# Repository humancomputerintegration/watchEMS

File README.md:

# Can a Smartwatch Move Your Fingers? 

This repository contains the source code used in the research publication "Can a Smartwatch Move Your Fingers?" from the [Human-Computer Integration Lab](https://lab.plopes.org/) at the University of Chicago.

## Citing

When using or building upon this device in an academic publication, please consider citing as follows:

ACM Reference Format: Akifumi Takahashi, Yudai Tanaka, Archit Tamhane, Alan Shen, Shan-Yuan Teng, and Pedro Lopes. 2024. Can a Smartwatch Move Your Fingers? Compact and Practical Electrical Muscle Stimulation in a Smartwatch. In The 37th Annual ACM Symposium on User Interface Software and Technology (UIST ’24), October 13–16, 2024, Pittsburgh, PA, USA. ACM, New York, NY, USA, 15 pages. https://doi.org/10.1145/3654777.3676373

## Contact

For any questions about this repository, please contact yudaitanaka@uchicago.edu

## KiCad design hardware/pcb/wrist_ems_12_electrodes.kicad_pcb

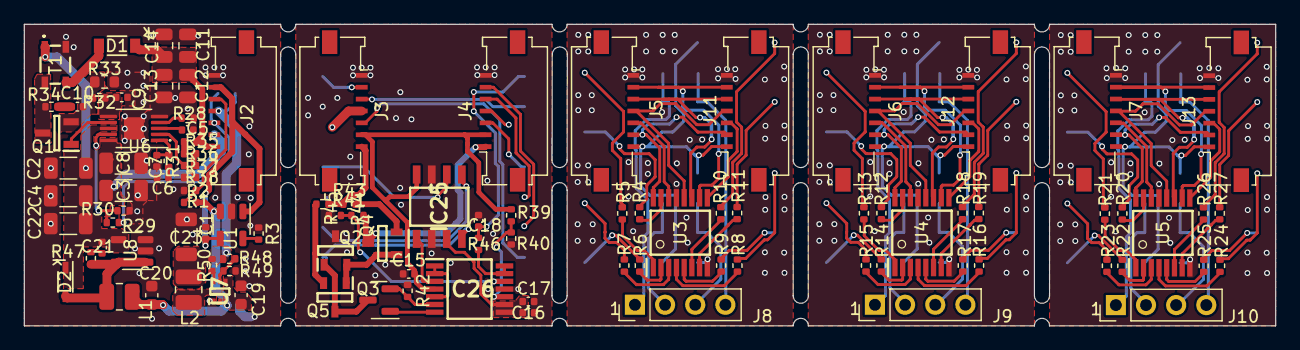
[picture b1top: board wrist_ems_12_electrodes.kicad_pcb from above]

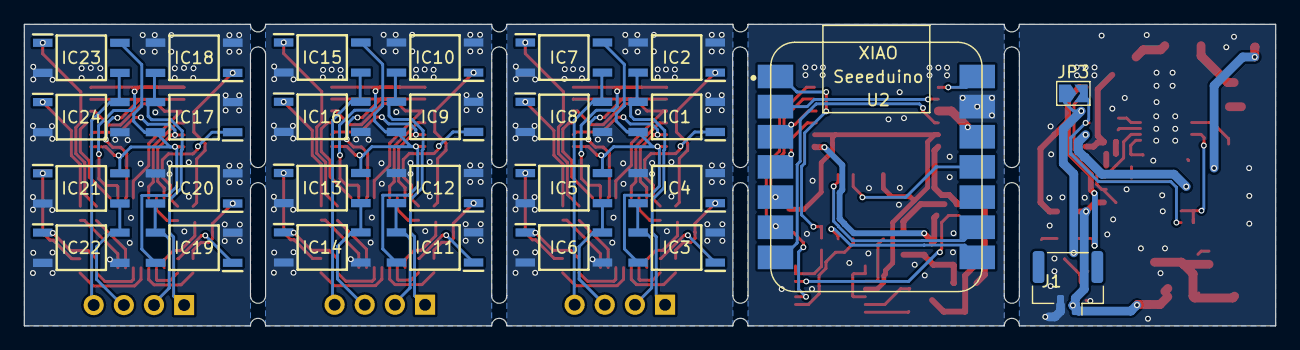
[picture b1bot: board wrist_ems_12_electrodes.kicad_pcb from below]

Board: 2 copper layers, 105.4 x 25.4 mm, 131 parts (27 on the bottom side), 140 nets.

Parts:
C1, C18: 1nF; C_0402_1005Metric
C2, C3, C4, C8, C22, C23: 47uF; C_1206_3216Metric
C5: 0.1uF; C_0402_1005Metric
C6: 22nF; C_0402_1005Metric
C7: 100pF; C_0402_1005Metric
C9: 10nF; C_0402_1005Metric
C10: 220pF; C_0402_1005Metric
C11, C12, C13, C14: 100nF; C_0805_2012Metric
C15, C16: 100nF; C_0402_1005Metric
C17: 10uF; C_0402_1005Metric
C19, C20: 4.7uF; C_0603_1608Metric
C21: 120pF; C_0402_1005Metric
D1: RF081MM2STR
D2: NSVR1020MW2T1G; SOD2512X110N
IC1, IC2, IC3, IC4, IC5, IC6, IC7, IC8, IC9, IC10, IC11, IC12, IC13, IC14, IC15, IC16, IC17, IC18, IC19, IC20, IC21, IC22, IC23, IC24: TLP188_TPL,E; SOP254P700X220-4N
IC25: DAC8830ID; SOIC127P600X175-8N
IC26: OPA4205APWT; SOP65P640X120-14N
J1: Conn_01x02_Pin; JST_GH_SM02B-GHS-TB_1x02-1MP_P1.25mm_Horizontal
J2, J3, J4, J5, J6, J7, J11, J12, J13: Conn_01x07_Pin; Molex_200528-0070_1x07-1MP_P1.00mm_Horizontal
J8, J9, J10: Conn_01x04_Pin; PinHeader_1x04_P2.54mm_Vertical
JP3: Jumper_2_Open; SolderJumper-2_P1.3mm_Open_TrianglePad1.0x1.5mm
L1: 4.7uH; L_1008_2520Metric
L2: 1uH; L_1008_2520Metric
Q1: RSR030N06TL; SOT95P280X100-3N
Q2, Q4, Q5: MMBTA92LT1G; SOT96P237X111-3N
Q3: DMN30H4D0L; SOT-23
R1, R2, R29, R49: 100k; R_0402_1005Metric
R3: 10k; R_0402_1005Metric
R4, R5, R6, R7, R8, R9, R10, R11, R12, R13, R14, R15, R16, R17, R18, R19, R20, R21, R22, R23, R24, R25, R26, R27: 330; R_0402_1005Metric
R28: 130k(100kHz); R_0402_1005Metric
R30: 240k; R_0402_1005Metric
R31: 6.8k; R_0402_1005Metric
R32, R34, R47: 22; R_0402_1005Metric
R33: 0.02; R_0603_1608Metric
R35, R36, R37, R50: 499k; R_0402_1005Metric
R38: 16k; R_0402_1005Metric
R39: 300k; R_0402_1005Metric
R40: 200k; R_0402_1005Metric
R41: 1k; R_0402_1005Metric
R42: 1k3; R_0402_1005Metric
R43, R46: 100; R_0402_1005Metric
R44: 1M; R_0402_1005Metric
R45: 30k; R_0402_1005Metric
R48: 453k; R_0402_1005Metric
T1: ATB322515-0110-T000; ATB3225150110T000
U1: MCP73812T-420I-OT; SOT-23-5
U2: SeeeduinoXIAO_onlyPinHeader; XIAO-nRF52840-Sense-14P-2.54-21X17.8MM)_onlyPins
U3, U4, U5: 74AHCT595; SOP65P640X110-16N
U6: LT3757AEMSE; MSOP-10-1EP_3x3mm_P0.5mm_EP1.68x1.88mm
U7: XPS62A01DRLR; SOTFL50P160X60-6N
U8: TPS613222ADBV; SOT-23-5

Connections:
3V3: J3.4, U2.12 (3V3)
5V: C15.2, IC25.8 (VDD), IC26.4 (V+), J3.6, J4.2, R39.2
150V: J3.7, R41.1, R43.1
/SR_PhotoSW_4ch_out1/CH1: IC9.3 (E), IC10.4 (C), J9.1
/SR_PhotoSW_4ch_out1/CH2: IC11.3 (E), IC12.4 (C), J9.2
/SR_PhotoSW_4ch_out1/CH3: IC13.3 (E), IC14.4 (C), J9.3
/SR_PhotoSW_4ch_out1/CH4: IC15.3 (E), IC16.4 (C), J9.4
/SR_PhotoSW_4ch_out1/SR1Q1: R12.2, U4.15 (QA)
/SR_PhotoSW_4ch_out1/SR1Q2: R13.2, U4.1 (QB)
/SR_PhotoSW_4ch_out1/SR1Q3: R14.2, U4.2 (QC)
/SR_PhotoSW_4ch_out1/SR1Q4: R15.2, U4.3 (QD)
/SR_PhotoSW_4ch_out1/SR1Q5: R16.2, U4.4 (QE)
/SR_PhotoSW_4ch_out1/SR1Q6: R17.2, U4.5 (QF)
/SR_PhotoSW_4ch_out1/SR1Q7: R18.2, U4.6 (QG)
/SR_PhotoSW_4ch_out1/SR1Q8: R19.2, U4.7 (QH)
/SR_PhotoSW_4ch_out2/CH1: IC17.3 (E), IC18.4 (C), J10.1
/SR_PhotoSW_4ch_out2/CH2: IC19.3 (E), IC20.4 (C), J10.2
/SR_PhotoSW_4ch_out2/CH3: IC21.3 (E), IC22.4 (C), J10.3
/SR_PhotoSW_4ch_out2/CH4: IC23.3 (E), IC24.4 (C), J10.4
/SR_PhotoSW_4ch_out2/SR1Q1: R20.2, U5.15 (QA)
/SR_PhotoSW_4ch_out2/SR1Q2: R21.2, U5.1 (QB)
/SR_PhotoSW_4ch_out2/SR1Q3: R22.2, U5.2 (QC)
/SR_PhotoSW_4ch_out2/SR1Q4: R23.2, U5.3 (QD)
/SR_PhotoSW_4ch_out2/SR1Q5: R24.2, U5.4 (QE)
/SR_PhotoSW_4ch_out2/SR1Q6: R25.2, U5.5 (QF)
/SR_PhotoSW_4ch_out2/SR1Q7: R26.2, U5.6 (QG)
/SR_PhotoSW_4ch_out2/SR1Q8: R27.2, U5.7 (QH)
/SR_PhotoSW_4ch_out/CH1: IC1.3 (E), IC2.4 (C), J8.1
/SR_PhotoSW_4ch_out/CH2: IC3.3 (E), IC4.4 (C), J8.2
/SR_PhotoSW_4ch_out/CH3: IC5.3 (E), IC6.4 (C), J8.3
/SR_PhotoSW_4ch_out/CH4: IC7.3 (E), IC8.4 (C), J8.4
/SR_PhotoSW_4ch_out/SR1Q1: R4.2, U3.15 (QA)
/SR_PhotoSW_4ch_out/SR1Q2: R5.2, U3.1 (QB)
/SR_PhotoSW_4ch_out/SR1Q3: R6.2, U3.2 (QC)
/SR_PhotoSW_4ch_out/SR1Q4: R7.2, U3.3 (QD)
/SR_PhotoSW_4ch_out/SR1Q5: R8.2, U3.4 (QE)
/SR_PhotoSW_4ch_out/SR1Q6: R9.2, U3.5 (QF)
/SR_PhotoSW_4ch_out/SR1Q7: R10.2, U3.6 (QG)
/SR_PhotoSW_4ch_out/SR1Q8: R11.2, U3.7 (QH)
/dcdc_5v_to_100V/Rsense: C10.2, Q1.2, R32.1, R33.2
/dcdc_5v_to_100V/Sense: C9.1, R32.2, U6.6 (SENSE)
/dcdc_5v_to_100V/dcdc_150V_SW: Q1.3, R34.1, T1.4
/dcdc_bat_to_3v3_5v/PG_3V3: R50.1, U7.6 (PG)
/dcdc_bat_to_3v3_5v/dcdc_3V3_SW: L2.1, U7.2 (SW)
/vol_to_curr/2V: C16.2, C17.2, IC25.3 (VREF), IC26.8, IC26.9 (-)
CLR: J4.6, U2.6 (PA9_A5_D5_SCL)
CUR_OUT: J4.1, Q4.3 (C), R44.1
CUR_vol: C18.2, R46.2, U2.1 (PA02_A0_D0)
DAC_MOSI: IC25.6 (SDI), U2.11 (PA6_A10_D10_MOSI)
DAC_SCK: IC25.5 (SCLK), U2.9 (PA7_A8_D8_SCK)
DAC_nCS: IC25.4 (~CS), U2.8 (PB09_A7_D7_RX)
DI: J4.3, U2.4 (PA11_A3_D3)
EN_150V: J3.5, U2.7 (PB08_A6_D6_TX)
GND: C15.1, C16.1, C17.1, C18.1, IC25.2 (AGND), IC25.7 (DGND), IC26.11 (V-), J3.1, J4.7, Q2.3 (C), R40.2, R42.2, R45.2, U2.13 (GND)
GNDA: C1.1, C2.2, C3.2, C4.2, C5.2, C6.2, C7.2, C8.2, C9.2, C11.2, C12.2, C13.2, C14.2, C19.2, C20.2, C22.2, C23.2, J1.2, J2.7, R2.2, R3.2, R28.1, R30.2, R33.1, R38.1, R49.2, T1.2, U1.2 (V_{SS}), U6.5 (SYNC), U6.11 (GND), U7.1 (GND), U8.2 (GND), U8.3 (NC)
unnamed: C6.1, R31.2
unnamed: C10.1, R34.2
unnamed: C21.1, R47.1
unnamed: D1.2 (A), T1.3
unnamed: D2.2 (A), L1.2, R47.2, U8.1 (SW), U8.5 (NC)
unnamed: IC1.1 (A), R4.1
unnamed: IC2.1 (A), R5.1
unnamed: IC3.1 (A), R6.1
unnamed: IC4.1 (A), R7.1
unnamed: IC5.1 (A), R8.1
unnamed: IC6.1 (A), R9.1
unnamed: IC7.1 (A), R10.1
unnamed: IC8.1 (A), R11.1
unnamed: IC9.1 (A), R12.1
unnamed: IC10.1 (A), R13.1
unnamed: IC11.1 (A), R14.1
unnamed: IC12.1 (A), R15.1
unnamed: IC13.1 (A), R16.1
unnamed: IC14.1 (A), R17.1
unnamed: IC15.1 (A), R18.1
unnamed: IC16.1 (A), R19.1
unnamed: IC17.1 (A), R20.1
unnamed: IC18.1 (A), R21.1
unnamed: IC19.1 (A), R22.1
unnamed: IC20.1 (A), R23.1
unnamed: IC21.1 (A), R24.1
unnamed: IC22.1 (A), R25.1
unnamed: IC23.1 (A), R26.1
unnamed: IC24.1 (A), R27.1
unnamed: IC25.1 (VOUT), IC26.3 (+)
unnamed: IC26.1, IC26.2 (-), IC26.5 (+)
unnamed: IC26.6 (-), Q3.2 (S), R42.1
unnamed: IC26.10 (+), R39.1, R40.1
unnamed: IC26.12 (+), R44.2, R45.1
unnamed: IC26.13 (-), IC26.14, R46.1
unnamed: Q2.1 (B), Q3.3 (D), Q5.3 (C)
unnamed: Q2.2 (E), Q4.1 (B), Q5.1 (B)
unnamed: IC26.7, Q3.1 (G)
unnamed: Q4.2 (E), R43.2
unnamed: Q5.2 (E), R41.2
unnamed: R35.1, R36.2
unnamed: R36.1, R37.2
unnamed: R3.1, U1.5 (PROG)
unnamed: R37.1, R38.2, U6.2 (FBX)
unnamed: Q1.1, U6.7 (GATE)
unnamed: R28.2, U6.4 (RT)
unnamed: C5.1, U6.3 (SS)
unnamed: C7.1, R31.1, U6.1 (VC)
unnamed: R29.1, R30.1, U6.9 (~SHDN/UVLO)
unnamed: R48.2, R49.1, U7.5 (FB)
RCK: J4.4, U2.3 (PA10_A2_D2)
SCK: J4.5, U2.5 (PA8_A4_D4_SDA)
Vbat: C19.1, C20.1, J1.1, L1.1, R1.1, U1.3 (V_{BAT}), U7.3 (VIN), U7.4 (EN)
bat_vol: J3.3, U2.2 (PA4_A1_D1)
dcdc_3V3: C23.1, J2.4, JP3.1 (A), L2.2, R48.1, R50.2
dcdc_5V: C2.1, C3.1, C4.1, C8.1, C21.2, C22.1, D2.1 (K), J2.2, T1.1, U6.8 (INTVCC), U6.10 (VIN), U8.4 (VOUT)
dcdc_150V: C11.1, C12.1, C13.1, C14.1, D1.1 (K), J2.1, R35.2
dcdc_EN_150V: J2.3, JP3.2 (B), R29.2
dcdc_bat_vol: J2.5, R1.2, R2.1
dcdc_usb_5V: C1.2, J2.6, U1.1 (CE), U1.4 (V_{DD})
sw1_5v: J5.6, J11.2, U3.16 (VCC)
sw1_clr: J5.2, J11.6, U3.10 (~SRCLR)
sw1_di: J5.5, U3.14 (SER)
sw1_do: J11.3, U3.9 (QH')
sw1_gnd: IC1.2 (K), IC2.2 (K), IC2.3 (E), IC3.2 (K), IC4.2 (K), IC4.3 (E), IC5.2 (K), IC6.2 (K), IC6.3 (E), IC7.2 (K), IC8.2 (K), IC8.3 (E), J5.1, J11.7, U3.8 (GND), U3.13 (~OE)
sw1_rck: J5.4, J11.4, U3.12 (RCLK)
sw1_sck: J5.3, J11.5, U3.11 (SRCLK)
sw1_vcc: IC1.4 (C), IC3.4 (C), IC5.4 (C), IC7.4 (C), J5.7, J11.1
sw2_5v: J6.6, J12.2, U4.16 (VCC)
sw2_clr: J6.2, J12.6, U4.10 (~SRCLR)
sw2_di: J6.5, U4.14 (SER)
sw2_gnd: IC9.2 (K), IC10.2 (K), IC10.3 (E), IC11.2 (K), IC12.2 (K), IC12.3 (E), IC13.2 (K), IC14.2 (K), IC14.3 (E), IC15.2 (K), IC16.2 (K), IC16.3 (E), J6.1, J12.7, U4.8 (GND), U4.13 (~OE)
sw2_rck: J6.4, J12.4, U4.12 (RCLK)
sw2_sck: J6.3, J12.5, U4.11 (SRCLK)
sw2_vcc: IC9.4 (C), IC11.4 (C), IC13.4 (C), IC15.4 (C), J6.7, J12.1
sw3_5v: J7.6, J13.2, U5.16 (VCC)
sw3_clr: J7.2, J13.6, U5.10 (~SRCLR)
sw3_di: J7.5, U5.14 (SER)
sw3_do: J13.3, U5.9 (QH')
sw3_gnd: IC17.2 (K), IC18.2 (K), IC18.3 (E), IC19.2 (K), IC20.2 (K), IC20.3 (E), IC21.2 (K), IC22.2 (K), IC22.3 (E), IC23.2 (K), IC24.2 (K), IC24.3 (E), J7.1, J13.7, U5.8 (GND), U5.13 (~OE)
sw3_rck: J7.4, J13.4, U5.12 (RCLK)
sw3_sck: J7.3, J13.5, U5.11 (SRCLK)
sw3_vcc: IC17.4 (C), IC19.4 (C), IC21.4 (C), IC23.4 (C), J7.7, J13.1
sw_do: J12.3, U4.9 (QH')
usb_5V: J3.2, U2.14 (5V)

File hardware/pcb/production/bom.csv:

Designator,Footprint,Quantity,Value,LCSC Part #,,,,
"C1, C18",0402,2,1nF,C1523,,,,
C10,0402,1,220pF,C1530,,,,
"C11, C12, C13, C14",0805,4,100nF,C5331016,,,,
"C15, C16",0402,2,100nF,C9900048290,,,,
C17,0402,1,10uF,C408132,,,,
"C19, C20",0603,2,4.7uF,C19666,,,,
"C2, C22, C23, C3, C4, C8",1206,6,47uF,C76659,,,,
C21,0402,1,120pF,C695379,,,,
C5,0402,1,0.1uF,C1525,,,,
C6,0402,1,22nF,C1532,,,,
C7,0402,1,100pF,C1546,,,,
C9,0402,1,10nF,C15195,,,,
D1,RF081MM2STR,1,RF081MM2STR,C509966,,,,
D2,SOD2512X110N,1,NSVR1020MW2T1G,C893984,,,,
"IC1, IC10, IC11, IC12, IC13, IC14, IC15, IC16, IC17, IC18, IC19, IC2, IC20, IC21, IC22, IC23, IC24, IC3, IC4, IC5, IC6, IC7, IC8, IC9",SOP254P700X220-4N,24,"TLP188_TPL,E",C4153840,,,,
IC25,SOIC127P600X175-8N,1,DAC8830ID,C42816,,,,
IC26,SOP65P640X120-14N,1,OPA4205APWT,C20345595,,,,
J1,JST_GH_SM02B-GHS-TB_1x02-1MP_P1.25mm_Horizontal,1,Conn_01x02_Pin,C189893,,,,
"J10, J8, J9",PinHeader_1x04_P2.54mm_Vertical,3,Conn_01x04_Pin,,,,,
"J11, J12, J13, J2, J3, J4, J5, J6, J7",Molex_200528-0070_1x07-1MP_P1.00mm_Horizontal,9,Conn_01x07_Pin,C6369987,,,,
JP3,SolderJumper-2_P1.3mm_Open_TrianglePad1.0x1.5mm,1,Jumper_2_Open,,,,,
L1,1008,1,4.7uH,C668313,,,,
L2,1008,1,1uH,C435392,,,,
Q1,SOT95P280X100-3N,1,RSR030N06TL,C126317,,,,
"Q2, Q4, Q5",SOT96P237X111-3N,3,MMBTA92LT1G,C82049,,,,
Q3,SOT-23,1,DMN30H4D0L,C461015,,,,
"R1, R2, R29, R49",0402,4,100k,C25741,,,,
"R10, R11, R12, R13, R14, R15, R16, R17, R18, R19, R20, R21, R22, R23, R24, R25, R26, R27, R4, R5, R6, R7, R8, R9",0402,24,330,C25104,,,,
R28,0402,1,130k(100kHz),C409851,,,,
R3,0402,1,2k,C4109,,,,
R30,0402,1,240k,C413113,,,,
R31,0402,1,6.8k,C409870,,,,
"R32, R34, R47",0402,3,22,C413049,,,,
R33,0603,1,0.02,C2088537,,,,
"R35, R36, R37",0402,3,499k, C2986233,,,,
R38,0402,1,16k,C409889,,,,
R39,0402,1,300k,C131560,,,,
R40,0402,1,200k,C131534,,,,
R41,0402,1,1k,C445596,,,,
R42,0402,1,1k3,C336808,,,,
R43,0402,1,100, C491157,,,,
R44,0402,1,1M,C413126,,,,
R45,0402,1,30k,C413010,,,,
R46,0402,1,100,C25077,,,,
R48,0402,1,453k,C27009,,,,
R50,0402,1,499k,C25793,,,,
T1,ATB3225150110T000,1,ATB322515-0110-T000,C415291,,,,
U1,SOT-23-5,1,MCP73812T-420I-OT,C144308,,,,
U2,XIAO-nRF52840-Sense-14P-2.54-21X17.8MM)_onlyPins,1,SeeeduinoXIAO_onlyPinHeader,,,,,
"U3, U4, U5",SOP65P640X110-16N,3,74AHCT595,C554707,,,,
U6,MSOP-10-1EP_3x3mm_P0.5mm_EP1.68x1.88mm,1,LT3757AEMSE,C671465,,,,
U7,SOTFL50P160X60-6N,1,XPS62A01DRLR,C5157937,,,,
U8,SOT-23-5,1,TPS613222ADBV,C2071163,,,,
,,,,,,,,
ffc calble,7pin pitch1mm 30mm,,0152670745,,,Molex,0152670745,https://www.digikey.com/en/products/detail/molex/0152670745/4427495
ffc calble,7pin pitch1mm 50mm,,0152670747,,,Molex,0152670747,https://www.digikey.com/en/products/detail/molex/0152670747/4427497
ffc calble,7pin pitch1mm 70mm,,0151670749,,,Molex,0151670749,https://www.digikey.com/en/products/detail/molex/0151670749/4426466
ffc calble,7pin pitch1mm 76mm,,10-07-A-0076-C-4-08-4-T,,,GCT,10-07-A-0076-C-4-08-4-T,https://www.digikey.jp/ja/products/detail/gct/10-07-A-0076-C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
ffc calble,7pin pitch1mm 50mm,,10-07-A-0050-C-4-08-4-T,,,GCT,10-07-A-0050-C-4-08-4-T,https://www.digikey.jp/ja/products/detail/gct/10-07-A-0050-C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
ffc calble,7pin pitch1mm 152mm,,10-07-A-0152-C-4-08-4-T,,,GCT,10-07-A-0152-C-4-08-4-T,https://www.digikey.jp/ja/products/detail/gct/10-07-A-0152-C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
ffc calble,7pin pitch1mm 100mm,,10-07-A-0101-C-4-08-4-T,,,GCT,10-07-A-0101-C-4-08-4-T,https://www.digikey.jp/ja/products/detail/gct/10-07-A-0101-C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
,,,,,,,,
battery,,,,,,,,https://www.amazon.com/gp/product/B09WK78594/ref=ppx_yo_dt_b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
,,,DTP401525(EZ3),,,,,https://www.marutsu.co.jp/pc/i/2228265/
J1,,,SM02B-SRSS-TB,,,,SM02B-SRSS-TB,https://www.digikey.jp/ja/products/detail/jst-sales-america-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
J1 housing,,,SHR-02V-S-B,,,,SHR-02V-S-B,https://www.digikey.jp/ja/products/detail/jst-sales-america-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

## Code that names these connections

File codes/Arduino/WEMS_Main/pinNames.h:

/** Pin name aliases
 *  
 *      somwhow "int PIN_VOL_CUR = P0_2;" or so didn't work well. so here I defined them using #define macro. 
 *      if you find a better way, please modify it.
 */
#ifndef PIN_NAMES_H
#define PIN_NAMES_H

#define  PIN_VOL_CUR    P0_2    //A0;
#define  PIN_VOL_BAT    P0_3    //A1;

#define  PIN_SR_RCK     P0_28   //D2;
#define  PIN_SR_DIN     P0_29   //D3;
#define  PIN_SR_SCK     P0_4    //D4;
#define  PIN_SR_CLR     P0_5    //D5;

#define  PIN_HiV_EN     P1_11   //D6;

//#define  PIN_DAC_SDA    P0_4    //D4;
//#define  PIN_DAC_SCL    P0_5    //D5;

#define  PIN_DAC_MOSI   P1_15    //D10;
#define  PIN_DAC_MISO   P1_14    //D9;
#define  PIN_DAC_SCK    P1_13    //D8;
#define  PIN_DAC_nCS    P1_12    //D7;

//#define  PIN_NC P1_14
#define  PIN_NC P0_5

#endif

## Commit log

2025-03-13 pcb+3dprint+codes
